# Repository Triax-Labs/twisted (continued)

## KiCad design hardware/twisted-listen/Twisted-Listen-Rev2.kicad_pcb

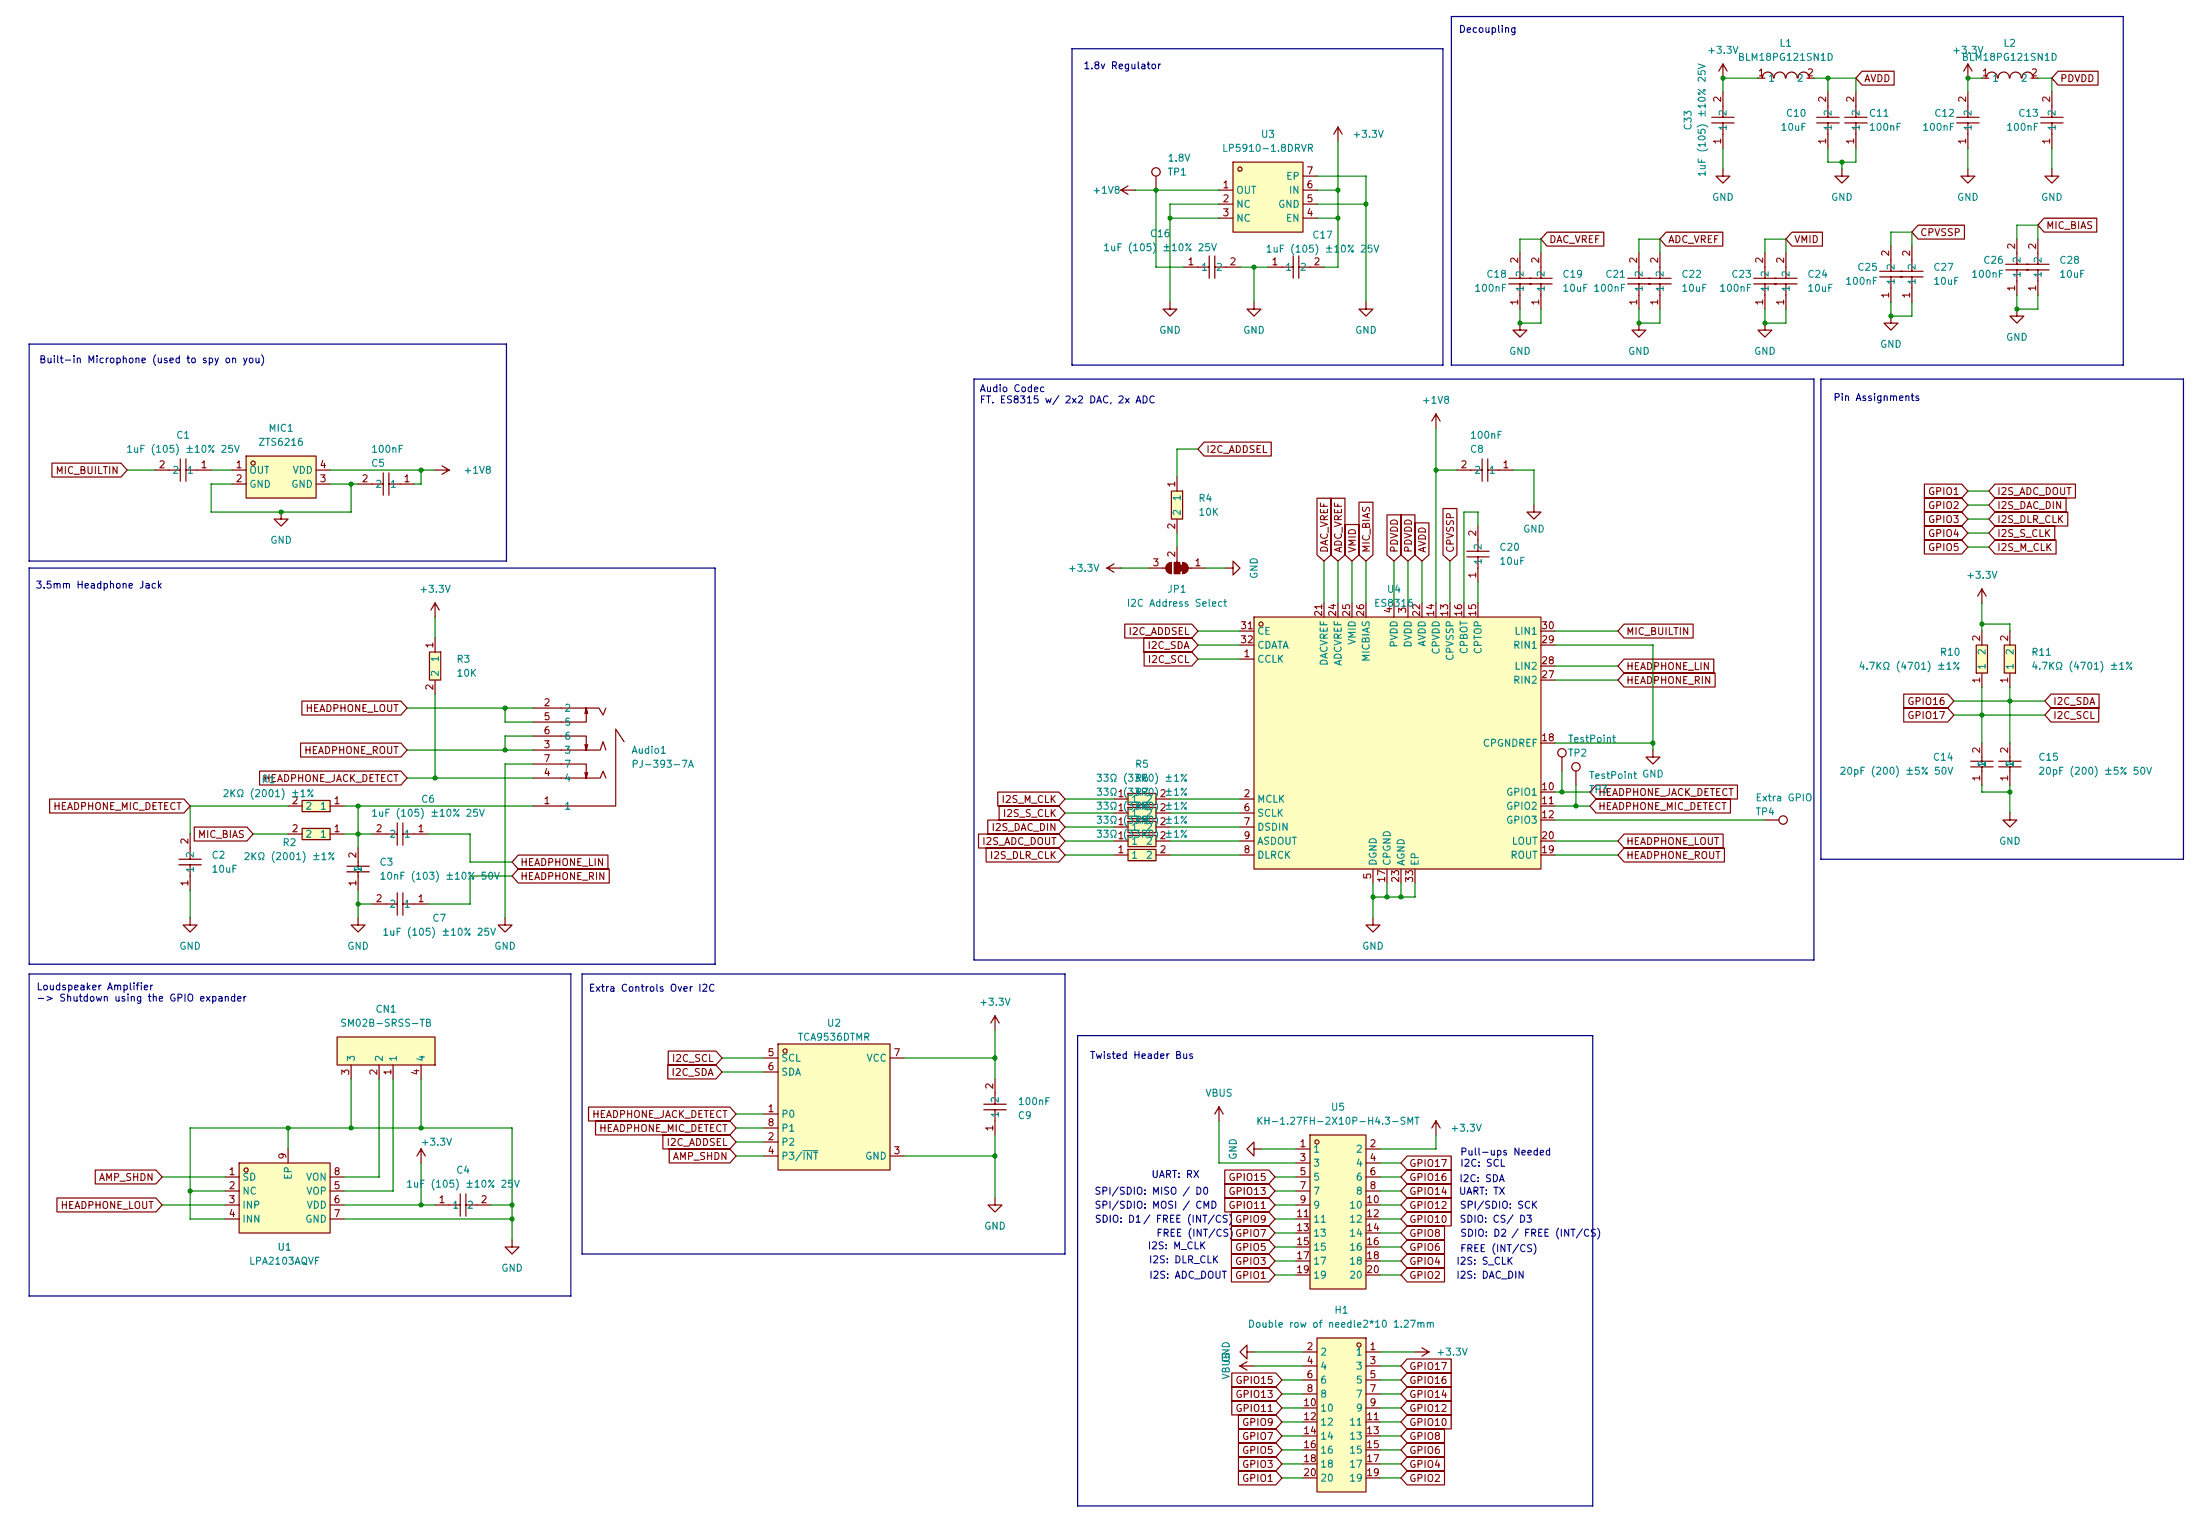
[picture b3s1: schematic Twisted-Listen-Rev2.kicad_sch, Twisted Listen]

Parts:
Audio1: PJ-393-7A; AUDIO-SMD_PJ-393-7A; MPN PJ-393-7A; LCSC Part C128990
C1, C4, C6, C7, C16, C17, C33: CL05A105KA5NQNC; C0402; MPN CL05A105KA5NQNC; LCSC Part C52923
C2, C10, C19, C20, C22, C24, C27, C28: CL05A106MP5NUNC_C315248; C0402; LCSC Part C315248
C3: CL05B103KB5NNNC; C0402; MPN CL05B103KB5NNNC; LCSC Part C15195
C5, C8, C9, C11, C12, C13, C18, C21, C23, C25, C26: CC0402KRX7R7BB104; C0402; LCSC Part C60474
C14, C15: 0402CG200J500NT; C0402; MPN 0402CG200J500NT; LCSC Part C1554
CN1: SM02B-SRSS-TB; CONN-SMD_2P-P1.00_SM02B-SRSS-TB-LF-SN; MPN SM02B-SRSS-TB(LF)(SN); LCSC Part C160402
H1: Double row of needle2*10 1.27mm; HDR-SMD_20P-P1.27-V-M-R2-C10-S1.27-LS5.5-1; MPN 1.27-2*10P立贴针; LCSC Part C59981
JP1: I2C Address Select; SolderJumper-3_P1.3mm_Bridged12_RoundedPad1.0x1.5mm
L1, L2: BLM18PG121SN1D; L0603; MPN BLM18PG121SN1D; LCSC Part C14709
MIC1: ZTS6216; MIC-SMD_4P-L2.8-W1.9-P1.84-TL; MPN ZTS6216; LCSC Part C481302
R1, R2: 0402WGF2001TCE; R0402; MPN 0402WGF2001TCE; LCSC Part C4109
R3, R4: 0402WGF1002TCE; R0402; LCSC Part C25744
R5, R6, R7, R8, R9: 0402WGF330JTCE; R0402; MPN 0402WGF330JTCE; LCSC Part C25105
R10, R11: 0402WGF4701TCE; R0402; MPN 0402WGF4701TCE; LCSC Part C25900
TP1: 1.8V; TinyTestPoint
TP2, TP3: TestPoint; TinyTestPoint
TP4: Extra GPIO; TinyTestPoint
U1: LPA2103AQVF; DFN-8_L2.0-W2.0-P0.50-BL-EP1.5; MPN LPA2103AQVF; LCSC Part C42460075
U2: TCA9536DTMR; X2SON-8_L1.4-W0.8-P0.50-BL; MPN TCA9536DTMR; LCSC Part C3190167
U3: LP5910-1.8DRVR; WSON-6_L2.0-W2.0-P0.65-TL-EP; MPN LP5910-1.8DRVR; LCSC Part C2867568
U4: ES8316; QFN-32_L4.0-W4.0-P0.40-BL-EP2.7; MPN ES8316; LCSC Part C365735
U5: KH-1.27FH-2X10P-H4.3-SMT; CONN-SMD_20P-P1.27_KINGHELM_KH-1.27FH-2X10P-H4.3-SMT; LCSC Part C2938399

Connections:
+1V8: C5.1, C8.2, C16.1, MIC1.4 (VDD), TP1.1 (1_1), U3.1 (OUT), U4.14 (CPVDD)
+3.3V: C4.1, C9.2, C12.2, C17.2, C33.2, H1.1, JP1.3 (B), L1.1, L2.1, R3.1, R10.2, R11.2, U1.6 (VDD), U2.7 (VCC), U3.4 (EN), U3.6 (IN), U5.2
ADC_VREF: C21.2, C22.2, U4.24 (ADCVREF)
AMP_SHDN: U1.1 (SD), U2.4 (P3/~INT)
AVDD: C10.2, C11.2, L1.2, U4.22 (AVDD)
CPVSSP: C25.2, C27.2, U4.13 (CPVSSP)
DAC_VREF: C18.2, C19.2, U4.21 (DACVREF)
GND: Audio1.7, C2.1, C3.1, C4.2, C5.2, C7.2, C8.1, C9.1, C10.1, C11.1, C12.1, C13.1, C14.1, C15.1, C16.2, C17.1, C18.1, C19.1, C21.1, C22.1, C23.1, C24.1, C25.1, C26.1, C27.1, C28.1, C33.1, CN1.3, CN1.4, H1.2, JP1.1 (A), MIC1.2 (GND), MIC1.3 (GND), U1.2 (NC), U1.4 (INN), U1.7 (GND), U1.9 (EP), U2.3 (GND), U3.2 (NC), U3.3 (NC), U3.5 (GND), U3.7 (EP), U4.5 (DGND), U4.17 (CPGND), U4.18 (CPGNDREF), U4.23 (AGND), U4.29 (RIN1), U4.33 (EP), U5.1
GPIO1: H1.20, R8.1, U5.19
GPIO2: H1.19, R7.1, U5.20
GPIO3: H1.18, R9.1, U5.17
GPIO4: H1.17, R6.1, U5.18
GPIO5: H1.16, R5.1, U5.15
GPIO6: H1.15, U5.16
GPIO7: H1.14, U5.13
GPIO8: H1.13, U5.14
GPIO9: H1.12, U5.11
GPIO10: H1.11, U5.12
GPIO11: H1.10, U5.9
GPIO12: H1.9, U5.10
GPIO13: H1.8, U5.7
GPIO14: H1.7, U5.8
GPIO15: H1.6, U5.5
GPIO16: C15.2, H1.5, R11.1, U2.6 (SDA), U4.32 (CDATA), U5.6
GPIO17: C14.2, H1.3, R10.1, U2.5 (SCL), U4.1 (CCLK), U5.4
HEADPHONE_JACK_DETECT: Audio1.4, R3.2, TP2.1 (1_1), U2.1 (P0), U4.10 (GPIO1)
HEADPHONE_LIN: C6.1, U4.28 (LIN2)
HEADPHONE_LOUT: Audio1.2, Audio1.5, U1.3 (INP), U4.20 (LOUT)
HEADPHONE_MIC_DETECT: C2.2, R1.2, TP3.1 (1_1), U2.8 (P1), U4.11 (GPIO2)
HEADPHONE_RIN: C7.1, U4.27 (RIN2)
HEADPHONE_ROUT: Audio1.3, Audio1.6, U4.19 (ROUT)
I2C_ADDSEL: R4.1, U2.2, U4.31 (CE)
MIC_BIAS: C26.2, C28.2, R2.2, U4.26 (MICBIAS)
MIC_BUILTIN: C1.2, U4.30 (LIN1)
unnamed: Audio1.1, C3.2, C6.2, R1.1, R2.1
unnamed: JP1.2 (C), R4.2
unnamed: C1.1, MIC1.1 (OUT)
unnamed: CN1.2, U1.8 (VON)
unnamed: CN1.1, U1.5 (VOP)
unnamed: R8.2, U4.9 (ASDOUT)
unnamed: C20.2, U4.16 (CPBOT)
unnamed: C20.1, U4.15 (CPTOP)
unnamed: R9.2, U4.8 (DLRCK)
unnamed: R7.2, U4.7 (DSDIN)
unnamed: TP4.1 (1_1), U4.12 (GPIO3)
unnamed: R5.2, U4.2 (MCLK)
unnamed: R6.2, U4.6 (SCLK)
PDVDD: C13.2, L2.2, U4.3 (DVDD), U4.4 (PVDD)
VBUS: H1.4, U5.3
VMID: C23.2, C24.2, U4.25 (VMID)

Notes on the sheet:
SPI/SDIO: MOSI / CMD
I2S: DLR_CLK
UART: TX
FREE (INT/CS)
1.8v Regulator
I2S: S_CLK
I2S: ADC_DOUT
Extra Controls Over I2C
Pin Assignments
UART: RX
Pull-ups Needed I2C: SCL
SDIO: D2
Built-in Microphone (used to spy on you)
SDIO: CS/ D3
SDIO: D1
/ FREE (INT/CS)
I2S: DAC_DIN
Loudspeaker Amplifier -> Shutdown using the GPIO expander
SPI/SDIO: MISO / D0
I2S: M_CLK
3.5mm Headphone Jack
Decoupling
Twisted Header Bus
SPI/SDIO: SCK
I2C: SDA
Audio Codec FT. ES8315 w/ 2x2 DAC, 2x ADC

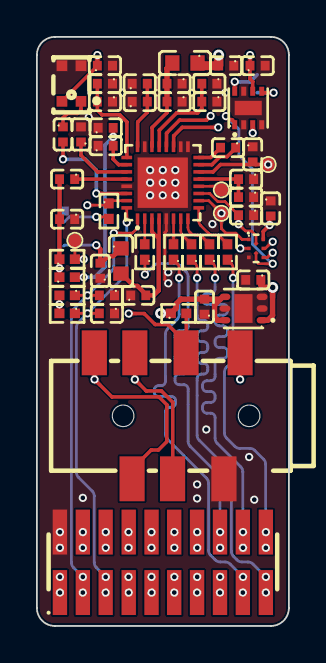
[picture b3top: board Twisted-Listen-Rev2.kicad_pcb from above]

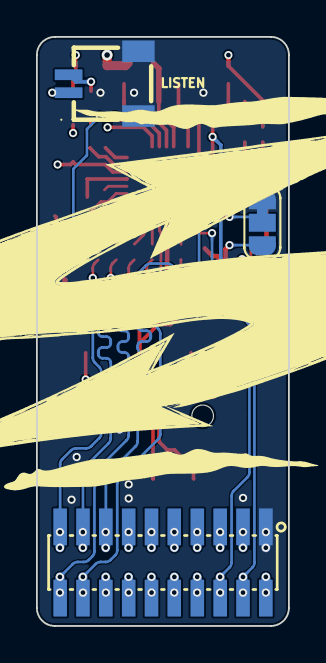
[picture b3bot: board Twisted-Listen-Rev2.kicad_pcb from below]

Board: 4 copper layers, 14.0 x 32.7 mm, 56 parts (3 on the bottom side), 50 nets.

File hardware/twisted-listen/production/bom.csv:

Designator,Footprint,Quantity,Value,LCSC Part #
AUDIO1,AUDIO-SMD_PJ-393-7A,1,PJ-393-7A,C128990
"C1, C16, C17, C33, C4, C6, C7",C0402,7,CL05A105KA5NQNC,C52923
"C10, C19, C2, C20, C22, C24, C27, C28",C0402,8,CL05A106MP5NUNC_C315248,C315248
"C11, C12, C13, C18, C21, C23, C25, C26, C5, C8, C9",C0402,11,CC0402KRX7R7BB104,C60474
"C14, C15",C0402,2,0402CG200J500NT,C1554
C3,C0402,1,CL05B103KB5NNNC,C15195
CN1,CONN-SMD_2P-P1.00_SM02B-SRSS-TB-LF-SN,1,SM02B-SRSS-TB,C160402
H1,HDR-SMD_20P-P1.27-V-M-R2-C10-S1.27-LS5.5-1,1,Double row of needle2*10 1.27mm,C59981
"L1, L2",L0603,2,BLM18PG121SN1D,C14709
MIC1,MIC-SMD_4P-L2.8-W1.9-P1.84-TL,1,ZTS6216,C481302
"R1, R2",R0402,2,0402WGF2001TCE,C4109
"R10, R11",R0402,2,0402WGF4701TCE,C25900
"R3, R4",R0402,2,0402WGF1002TCE,C25744
"R5, R6, R7, R8, R9",R0402,5,0402WGF330JTCE,C25105
"TP1, TP2, TP3, TP4",TinyTestPoint,4,TestPoint,
U1,DFN-8_L2.0-W2.0-P0.50-BL-EP1.5,1,LPA2103AQVF,C42460075
U2,X2SON-8_L1.4-W0.8-P0.50-BL,1,TCA9536DTMR,C3190167
U3,WSON-6_L2.0-W2.0-P0.65-TL-EP,1,LP5910-1.8DRVR,C2867568
U4,QFN-32_L4.0-W4.0-P0.40-BL-EP2.7,1,ES8316,C365735
U5,CONN-SMD_20P-P1.27_KINGHELM_KH-1.27FH-2X10P-H4.3-SMT,1,KH-1.27FH-2X10P-H4.3-SMT,C2938399

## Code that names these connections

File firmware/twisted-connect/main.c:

#include "ch32fun.h"
#include <stdio.h>

// use defines to make more meaningful names for our GPIO pins
#define PIN_1 PA4
#define PIN_K PA5
#define PIN_BOB PA8
#define PIN_KEVIN PA9

int main()
{
	SystemInit();

	funGpioInitAll(); // no-op on ch5xx

	funPinMode( PIN_1,     GPIO_CFGLR_OUT_10Mhz_PP ); // Set PIN_1 to output
	funPinMode( PIN_K,     GPIO_CFGLR_OUT_10Mhz_PP ); // Set PIN_K to output
	funPinMode( PIN_BOB,   GPIO_CFGLR_OUT_10Mhz_PP ); // Set PIN_BOB to output
	funPinMode( PIN_KEVIN, GPIO_CFGLR_OUT_10Mhz_PP ); // Set PIN_KEVIN to output


	while(1)
	{
		funDigitalWrite( PIN_1,     FUN_HIGH ); // Turn on PIN_1
		funDigitalWrite( PIN_K,     FUN_HIGH ); // Turn on PIN_K
		funDigitalWrite( PIN_BOB,   FUN_HIGH ); // Turn on PIN_BOB
		funDigitalWrite( PIN_KEVIN, FUN_HIGH ); // Turn on PIN_KEVIN
		Delay_Ms( 250 );
		funDigitalWrite( PIN_1,     FUN_LOW );  // Turn off PIN_1
		funDigitalWrite( PIN_K,     FUN_LOW );  // Turn off PIN_K
		funDigitalWrite( PIN_BOB,   FUN_LOW );  // Turn off PIN_BOB
		funDigitalWrite( PIN_KEVIN, FUN_LOW );  // Turn off PIN_KEVIN
		Delay_Ms( 250 );
	}
}
